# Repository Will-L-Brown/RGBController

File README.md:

# RGBController
Controller for RGB Strips and RGB Fans

Based on an Arduino Pro Micro (cheap chinese clone) 

Uses the FastLED library

Pin assignments can be found in the code

Recommended to have a resistor on the data output pins to the LED strips and fans, between 220Ω and 470Ω. I use 330Ω.

# 10-channel RGB Controller Hardware

This board is a custom board designed for hooking up to 10 aRGB devices with individual control using an Arduino Pro Micro. 

The Board features 9 3-pin aRGB headers and 1 Corsair RGB header. Idea is to have up to 8 RGB fans that are each individually addressable but do not pass the line back to have a combined effect, 
while also having a chain of Corsair RGB products and an aRGB strip.

There is a 3-button header for up to 3 standard case buttons, such as the unused reset switch!

This board is in a standard 2.5 inch drive format with mounting holes for easy case mounting.

# Known Hardware issues

- Rev 0.1A 
	- Incorrect pinout on the Corsair header
	
- Rev 0.1B
	- Corsair header does not have the best routing on VCC and GND to local filter capacitors
		- SMD stencil is compatible with Rev 0.1A hardware
	- BOM P/N for aRGB headers is incorrect. Correct part should be a 2.54mm spaced, 0.6mm diameter, right angle "Swiss machine pin" header to be compatible with standard aRGB connectors
		- I don't know of a good part number or source for this part. Contact me if you have a part number, or submit a pull request
	- BOM P/N for Molex power connect is likely not optimal. 
	- Spacing for aRGB headers may not be optimal for certain devices and may have clearance issues when completely populated
	- 0.1uF caps C12-16, C27-31 should not be populated. These destroy the signal from the ATMega and were intended for 5V-GND, not Din-GND

# Future Hardware To-Do

- Rev 0.1C
	- Re-routing filter caps for the Corsair header for better performace
- Future Variants
	- Change one aRGB header to a second Corsair header
	- Variant with 3 aRGB, 2 Cosair on one side, temp probes and fan headers on the other

# Off-The-Shelf components and LED Type
This is meant to use a variety of standard PC components as well as cheap RGB strips to produce the RGB effect.

A small list of various verified parts and their LED type are listed below:

- Corsair HD1x0 fans
    - WS2812B-based custom RGB modules
	- HD120: 12 LEDS
- Corsair XD5 Pump and Res Combo
    - WS2812B-based custom RGB modules
	- 10 LEDS
- Corsair XG7 RTX 2080 GPU Block
	- WS2812B-based custom RGB modules
	- 16 LEDS

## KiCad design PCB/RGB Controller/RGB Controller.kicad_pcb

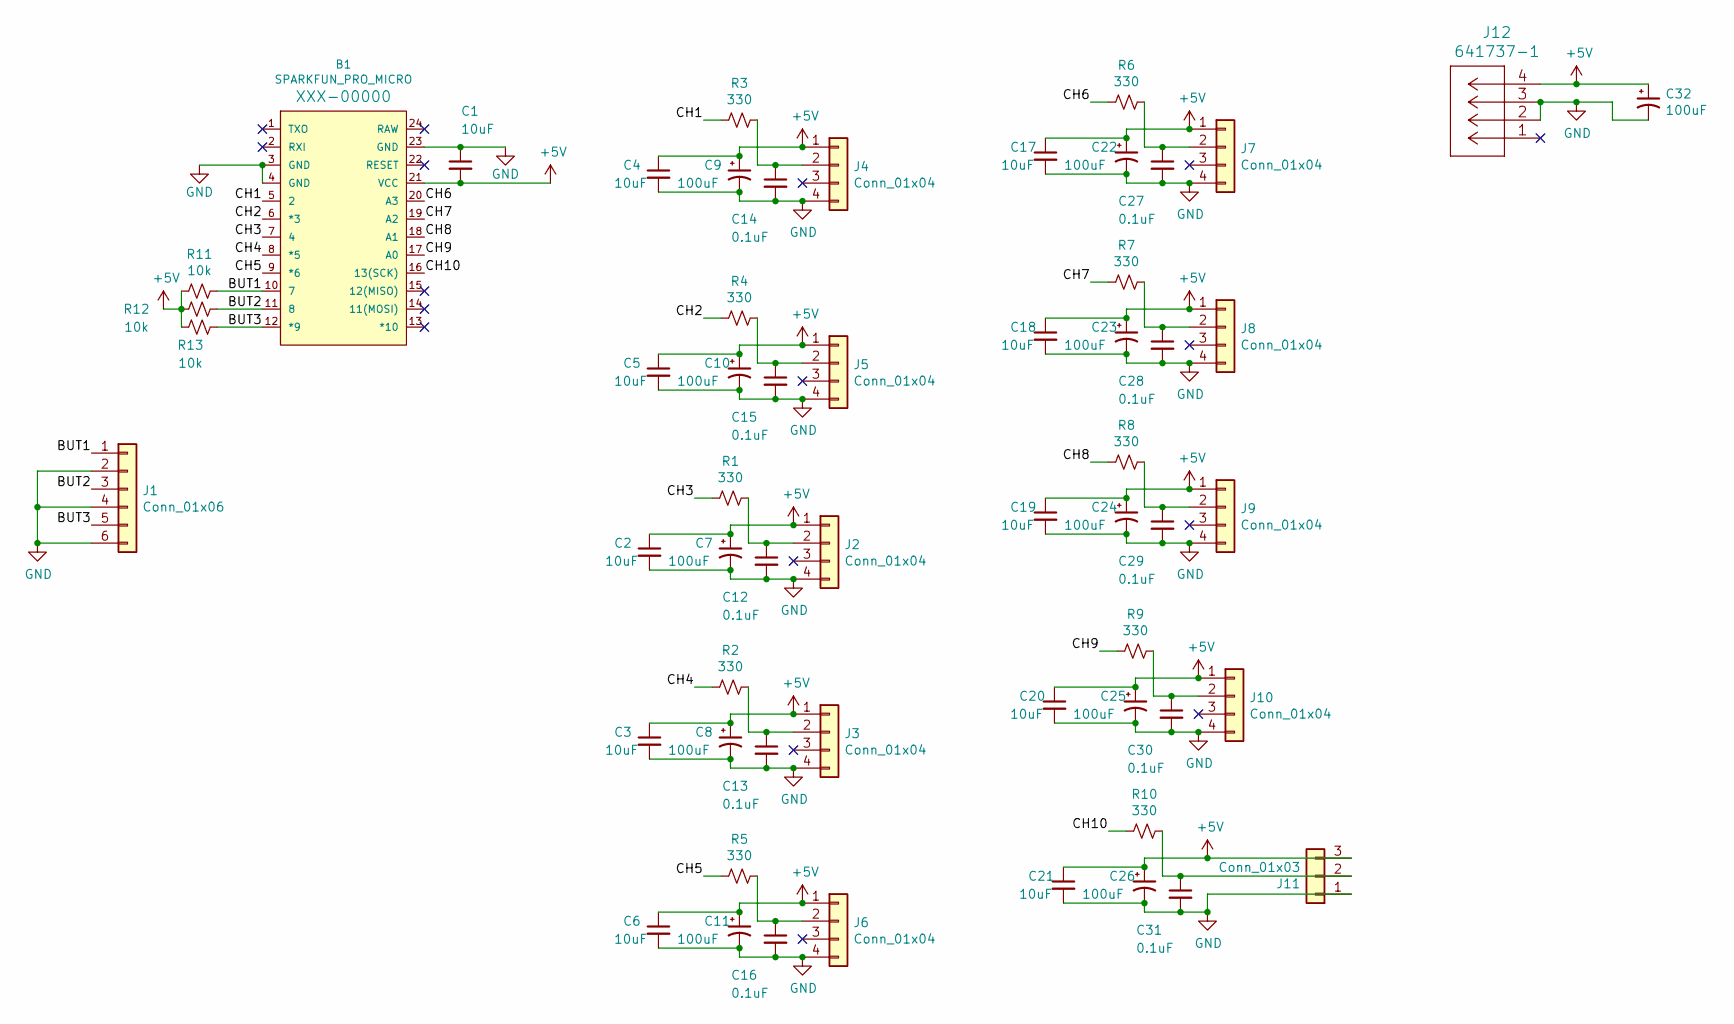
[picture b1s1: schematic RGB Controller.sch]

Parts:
B1: SPARKFUN_PRO_MICRO; MPN Pro Micro
C1, C2, C3, C4, C5, C6, C17, C18, C19, C20, C21: 10uF; C_0603_1608Metric_Pad1.08x0.95mm_HandSolder; MPN CL10A106MQ8NNNC; Digi-Key_PN 1276-1119-1-ND
C7, C8, C9, C10, C11, C22, C23, C24, C25, C26, C32: 100uF; UWR1A101MCL1GB; MPN UWR1A101MCL1GB; Digi-Key_PN 493-14561-1-ND
C12, C13, C14, C15, C16, C27, C28, C29, C30, C31: 0.1uF; C_0402_1005Metric_Pad0.74x0.62mm_HandSolder; MPN GRM155R71C104KA88D; Digi-Key_PN 490-3261-1-ND
J1: Conn_01x06; PinHeader_1x06_P2.54mm_Horizontal
J2, J3, J4, J5, J6, J7, J8, J9, J10: Conn_01x04; PinHeader_1x04_P2.54mm_Horizontal; MPN 830-10-004-20-001101; Digi-Key_PN 1212-1309-ND
J11: Conn_01x03; 70555-0002; MPN 70555-0002; Digi-Key_PN WM4176-ND
J12: 641737-1; 827001-2; MPN 641737-1; Digi-Key_PN A25430-ND
R1, R2, R3, R4, R5, R6, R7, R8, R9, R10: 330; R_0402_1005Metric_Pad0.72x0.64mm_HandSolder; MPN CRGCQ0402F330R; Digi-Key_PN A129621CT-ND
R11, R12, R13: 10k; R_0402_1005Metric_Pad0.72x0.64mm_HandSolder; MPN ERJ-2RKF1002X; Digi-Key_PN P10.0KLCT-ND

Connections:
+5V: B1.21 (VCC), C1.2, C2.1, C3.1, C4.1, C5.1, C6.1, C7.1, C8.1, C9.1, C10.1, C11.1, C17.1, C18.1, C19.1, C20.1, C21.1, C22.1, C23.1, C24.1, C25.1, C26.1, C32.1, J2.1, J3.1, J4.1, J5.1, J6.1, J7.1, J8.1, J9.1, J10.1, J11.3, J12.4, R11.2, R12.2, R13.2
/BUT1: B1.10 (7), J1.1, R11.1
/BUT2: B1.11 (8), J1.3, R12.1
/BUT3: B1.12 (*9), J1.5, R13.1
/CH1: B1.5 (2), R3.2
/CH2: B1.6 (*3), R4.2
/CH3: B1.7 (4), R1.2
/CH4: B1.8 (*5), R2.2
/CH5: B1.9 (*6), R5.2
/CH6: B1.20 (A3), R6.2
/CH7: B1.19 (A2), R7.2
/CH8: B1.18 (A1), R8.2
/CH9: B1.17 (A0), R9.2
/CH10: B1.16 (13(SCK)), R10.2
GND: B1.3 (GND), B1.4 (GND), B1.23 (GND), C1.1, C2.2, C3.2, C4.2, C5.2, C6.2, C7.2, C8.2, C9.2, C10.2, C11.2, C12.2, C13.2, C14.2, C15.2, C16.2, C17.2, C18.2, C19.2, C20.2, C21.2, C22.2, C23.2, C24.2, C25.2, C26.2, C27.2, C28.2, C29.2, C30.2, C31.2, C32.2, J1.2, J1.4, J1.6, J2.4, J3.4, J4.4, J5.4, J6.4, J7.4, J8.4, J9.4, J10.4, J11.1, J12.2, J12.3
unnamed: C12.1, J2.2, R1.1
unnamed: C13.1, J3.2, R2.1
unnamed: C14.1, J4.2, R3.1
unnamed: C15.1, J5.2, R4.1
unnamed: C16.1, J6.2, R5.1
unnamed: C27.1, J7.2, R6.1
unnamed: C28.1, J8.2, R7.1
unnamed: C29.1, J9.2, R8.1
unnamed: C30.1, J10.2, R9.1
unnamed: C31.1, J11.2, R10.1

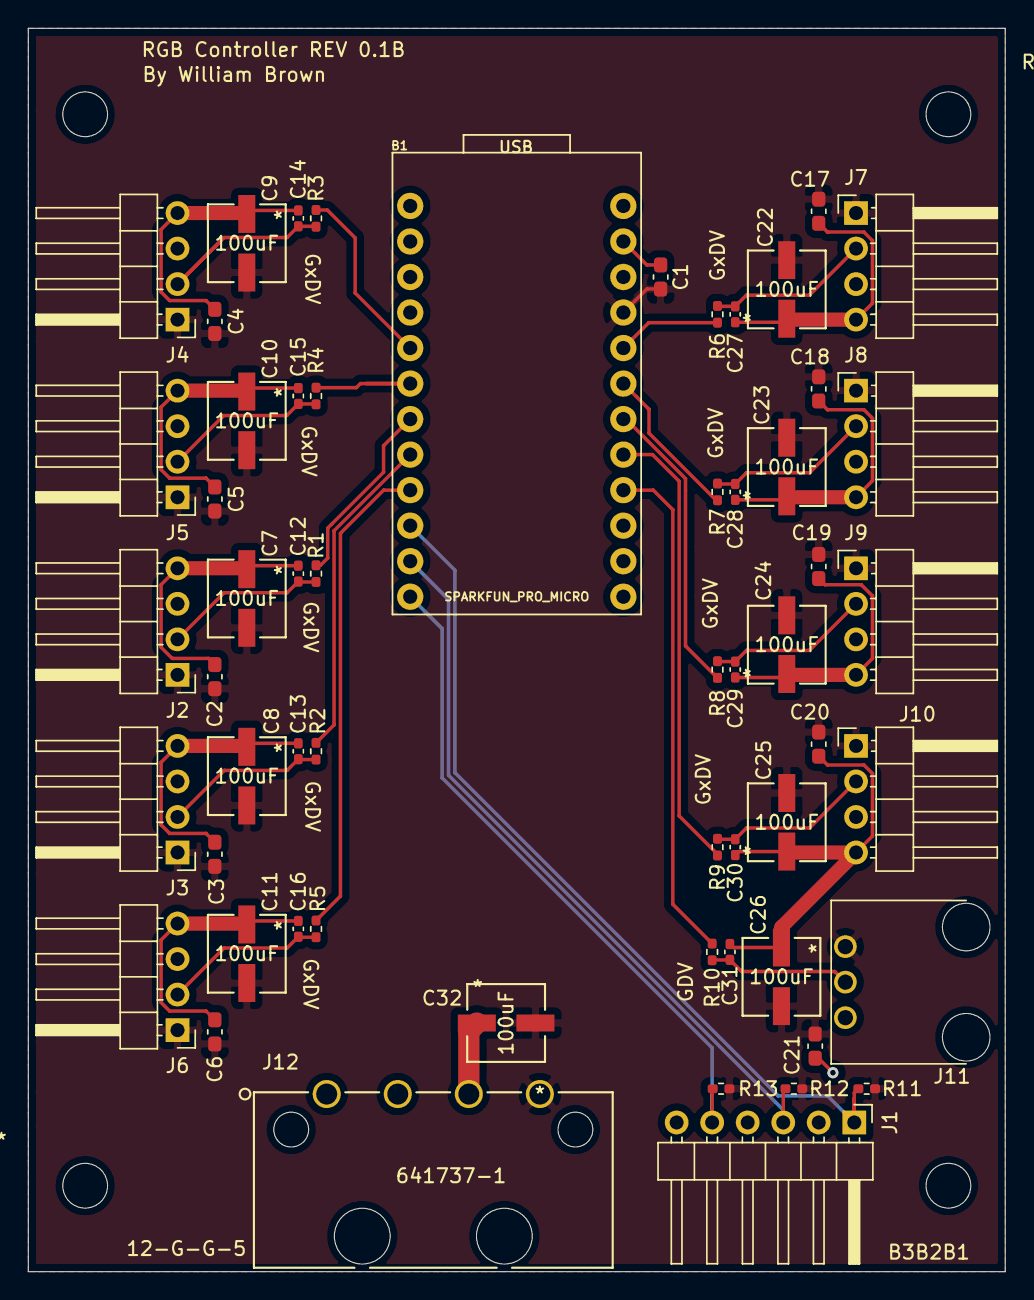
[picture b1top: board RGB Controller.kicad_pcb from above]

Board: 2 copper layers, 69.9 x 88.9 mm, 58 parts (0 on the bottom side), 25 nets.

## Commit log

2019-08-17 Update README.md
    Expanded information on what does what
2019-08-26 Added XG7 documentation and support
2020-02-20 Fixed formatting
2020-11-30 Rev 0.1A hardware
2020-11-30 Rev 0.1B hardware - Fixes Corsair Header pinout, 0.1A stencil compatible
2020-11-30 Updated README.md to document hardware
2020-11-30 Updated issues list

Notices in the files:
parts and their libraries:
Copyright 2016 Accelerated Designs. All rights reserved.
